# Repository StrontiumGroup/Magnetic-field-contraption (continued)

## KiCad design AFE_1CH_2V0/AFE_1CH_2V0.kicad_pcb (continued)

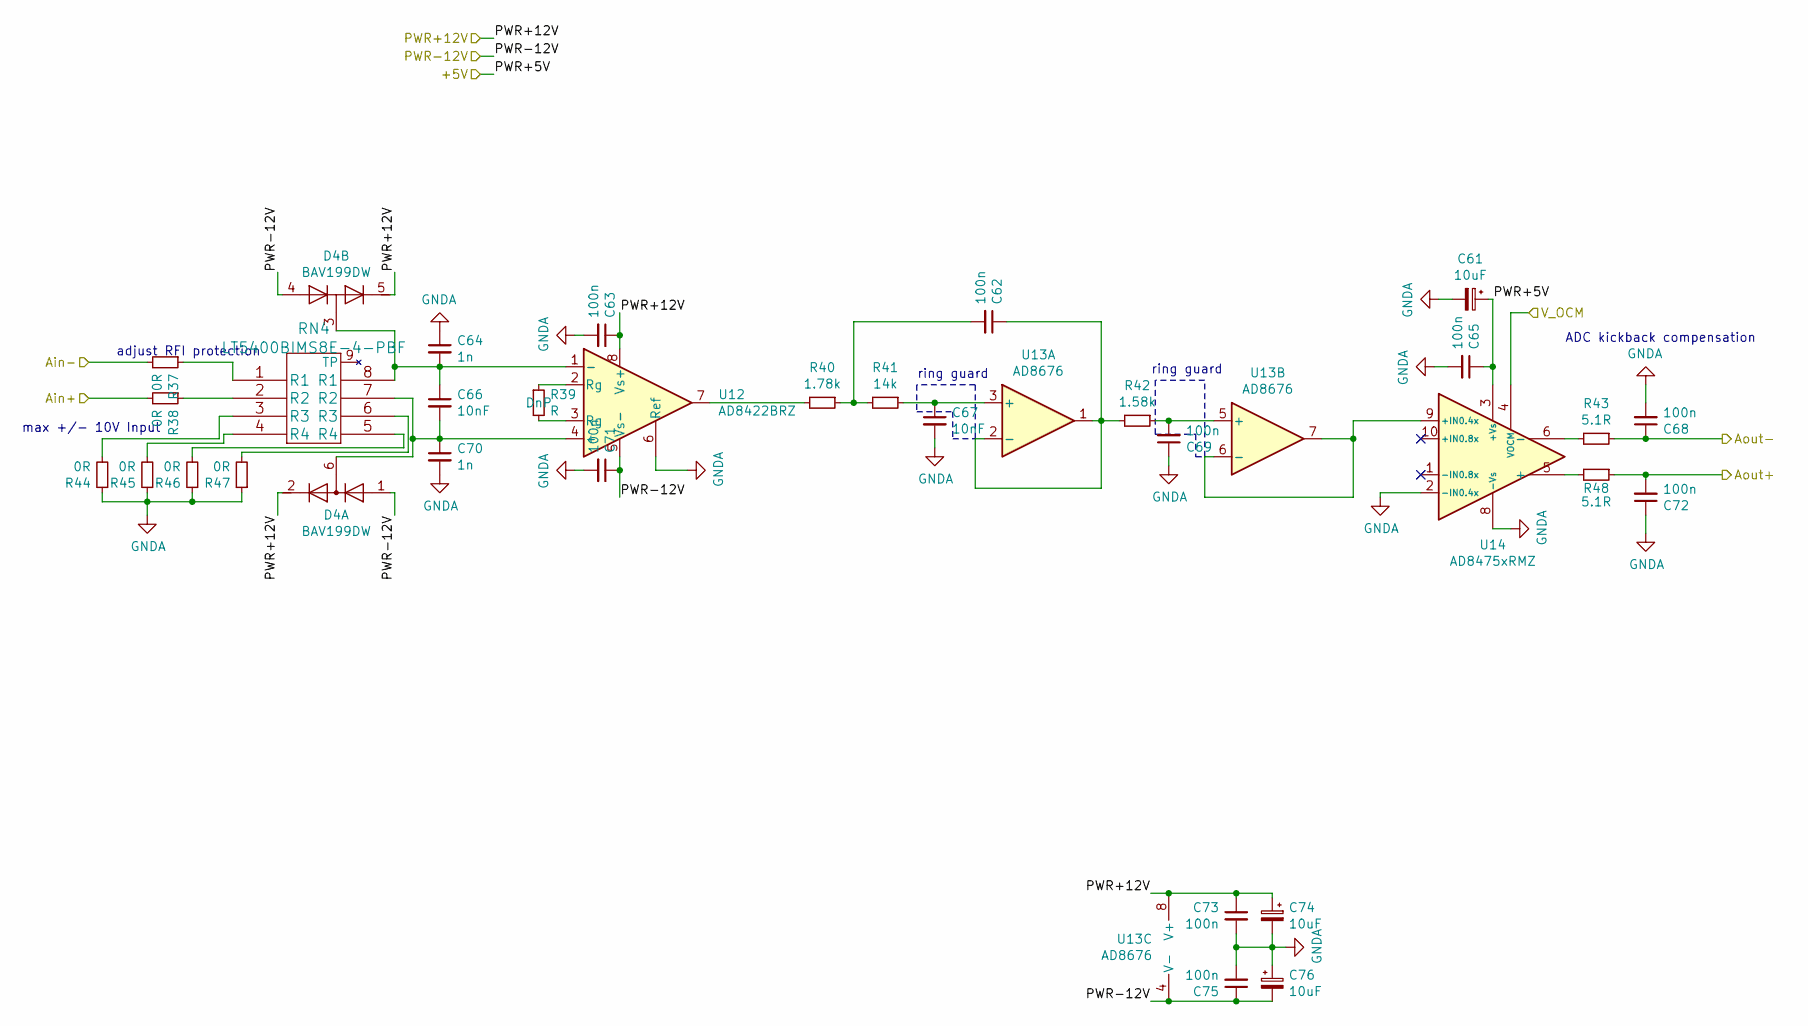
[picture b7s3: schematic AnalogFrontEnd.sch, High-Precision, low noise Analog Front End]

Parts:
C13, C26, C28: 10uF; CP_Elec_4x5.4; DigiKey 399-6695-1-ND
C14, C15, C20, C21, C23, C24: 100n; C_0805_2012Metric; DigiKey 399-1171-1-ND
C16, C22: 1n; C_0805_2012Metric; DigiKey 1276-1020-1-ND
C17, C25, C27: 100n; C_0805_2012Metric; DigiKey 399-1169-1-ND
C18, C19: 10nF; C_0805_2012Metric; DigiKey 1276-1245-1-ND
D1: BAV199DW; SOT-363_SC-70-6; DigiKey BAV199DW-FDITR-ND
R1, R2, R8, R9, R10, R11: 0R; R_0603_1608Metric; DigiKey 311-0.0GRCT-ND
R3: R; R_0805_2012Metric
R4: 1.78k; R_0805_2012Metric; DigiKey 541-1.78KCCT-ND
R5: 14k; R_0805_2012Metric; DigiKey 541-14.0KCCT-ND
R6: 1.58k; R_0805_2012Metric; DigiKey 541-1.58KCCT-ND
R7, R12: 5.1R; R_0805_2012Metric; DigiKey 541-5.10CCCT-ND
RN1: LT5400BIMS8E-4-PBF; MSOP-8-1EP_3x3mm_P0.65mm_EP1.68x1.88mm; DigiKey LT5400BIMS8E-4#PBF-ND
U3: AD8422BRZ; SOIC-8_3.9x4.9mm_P1.27mm; DigiKey AD8422ARZ-R7CT-ND
U4: AD8676; SOIC-8_3.9x4.9mm_P1.27mm
U5: AD8475xRMZ; MSOP-10_3x3mm_P0.5mm

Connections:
/AFE1/Ain+: R2.2; also elsewhere on the board
/AFE1/Ain-: R1.2; also elsewhere on the board
/AFE1/Aout+: C24.2, R12.1; also elsewhere on the board
/AFE1/Aout-: C20.1, R7.1; also elsewhere on the board
/PWR+5V: C13.1, C17.1, U5.3 (+Vs); also elsewhere on the board
/PWR+12V: C15.1, C25.1, C26.1, D1.2 (K2), D1.5 (K4), U3.8 (Vs+), U4.8 (V+); also elsewhere on the board
/PWR-12V: C23.1, C27.1, C28.2, D1.1 (A1), D1.4 (A3), U3.5 (Vs-), U4.4 (V-); also elsewhere on the board
/V_OCM: U5.4 (VOCM); also elsewhere on the board
GNDA: C13.2, C15.2, C16.1, C17.2, C19.2, C20.2, C21.1, C22.2, C23.2, C24.1, C25.2, C26.2, C27.2, C28.1, R8.1, R9.1, R10.1, R11.1, U3.6 (Ref), U5.2 (-IN0.4x), U5.8 (-Vs); also elsewhere on the board
unnamed: C14.1, R6.2, U4.1, U4.2 (-)
unnamed: C14.2, R4.1, R5.2
unnamed: C16.2, C18.1, D1.3 (K1A2), RN1.8 (R1), U3.1 (-)
unnamed: C18.2, C22.1, D1.6 (K3A4), RN1.7 (R2), U3.4 (+)
unnamed: C19.1, R5.1, U4.3 (+)
unnamed: C21.2, R6.1, U4.5 (+)
unnamed: R1.1, RN1.1 (R1)
unnamed: R2.1, RN1.2 (R2)
unnamed: R3.1, U3.2 (Rg)
unnamed: R3.2, U3.3 (Rg)
unnamed: R4.2, U3.7
unnamed: R7.2, U5.6 (-)
unnamed: R8.2, RN1.3 (R3)
unnamed: R9.2, RN1.4 (R4)
unnamed: R10.2, RN1.5 (R4)
unnamed: R11.2, RN1.6 (R3)
unnamed: R12.2, U5.5 (+)
unnamed: U4.6 (-), U4.7, U5.9 (+IN0.4x)

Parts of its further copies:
C29, C42, C44, C45, C58, C60, C61, C74, C76: 10uF; CP_Elec_4x5.4; DigiKey 399-6695-1-ND
C30, C31, C36, C37, C39, C40, C46, C47, C52, C53, C55, C56, C62, C63, C68, C69, C71, C72: 100n; C_0805_2012Metric; DigiKey 399-1171-1-ND
C32, C38, C48, C54, C64, C70: 1n; C_0805_2012Metric; DigiKey 1276-1020-1-ND
C33, C41, C43, C49, C57, C59, C65, C73, C75: 100n; C_0805_2012Metric; DigiKey 399-1169-1-ND
C34, C35, C50, C51, C66, C67: 10nF; C_0805_2012Metric; DigiKey 1276-1245-1-ND
D2, D3, D4: BAV199DW; SOT-363_SC-70-6; DigiKey BAV199DW-FDITR-ND
R13, R14, R20, R21, R22, R23, R25, R26, R32, R33, R34, R35, R37, R38, R44, R45, R46, R47: 0R; R_0603_1608Metric; DigiKey 311-0.0GRCT-ND
R15, R27, R39: R; R_0805_2012Metric
R16, R28, R40: 1.78k; R_0805_2012Metric; DigiKey 541-1.78KCCT-ND
R17, R29, R41: 14k; R_0805_2012Metric; DigiKey 541-14.0KCCT-ND
R18, R30, R42: 1.58k; R_0805_2012Metric; DigiKey 541-1.58KCCT-ND
R19, R24, R31, R36, R43, R48: 5.1R; R_0805_2012Metric; DigiKey 541-5.10CCCT-ND
RN2, RN3, RN4: LT5400BIMS8E-4-PBF; MSOP-8-1EP_3x3mm_P0.65mm_EP1.68x1.88mm; DigiKey LT5400BIMS8E-4#PBF-ND
U6, U9, U12: AD8422BRZ; SOIC-8_3.9x4.9mm_P1.27mm; DigiKey AD8422ARZ-R7CT-ND
U7, U10, U13: AD8676; SOIC-8_3.9x4.9mm_P1.27mm
U8, U11, U14: AD8475xRMZ; MSOP-10_3x3mm_P0.5mm

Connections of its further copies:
/AFE2/Ain+: R14.2; also elsewhere on the board
/AFE2/Ain-: R13.2; also elsewhere on the board
/AFE2/Aout+: C40.2, R24.1; also elsewhere on the board
/AFE2/Aout-: C36.1, R19.1; also elsewhere on the board
/AFE3/Ain+: R26.2; also elsewhere on the board
/AFE3/Ain-: R25.2; also elsewhere on the board
/AFE3/Aout+: C56.2, R36.1; also elsewhere on the board
/AFE3/Aout-: C52.1, R31.1; also elsewhere on the board
/AFE4/Ain+: R38.2; also elsewhere on the board
/AFE4/Ain-: R37.2; also elsewhere on the board
/AFE4/Aout+: C72.2, R48.1; also elsewhere on the board
/AFE4/Aout-: C68.1, R43.1; also elsewhere on the board
/PWR+5V: C29.1, C33.1, C45.1, C49.1, C61.1, C65.1, U8.3 (+Vs), U11.3 (+Vs), U14.3 (+Vs); also elsewhere on the board
/PWR+12V: C31.1, C41.1, C42.1, C47.1, C57.1, C58.1, C63.1, C73.1, C74.1, D2.2 (K2), D2.5 (K4), D3.2 (K2), D3.5 (K4), D4.2 (K2), D4.5 (K4), U6.8 (Vs+), U7.8 (V+), U9.8 (Vs+), U10.8 (V+), U12.8 (Vs+), U13.8 (V+); also elsewhere on the board
/PWR-12V: C39.1, C43.1, C44.2, C55.1, C59.1, C60.2, C71.1, C75.1, C76.2, D2.1 (A1), D2.4 (A3), D3.1 (A1), D3.4 (A3), D4.1 (A1), D4.4 (A3), U6.5 (Vs-), U7.4 (V-), U9.5 (Vs-), U10.4 (V-), U12.5 (Vs-), U13.4 (V-); also elsewhere on the board
/V_OCM: U8.4 (VOCM), U11.4 (VOCM), U14.4 (VOCM); also elsewhere on the board
GNDA: C29.2, C31.2, C32.1, C33.2, C35.2, C36.2, C37.1, C38.2, C39.2, C40.1, C41.2, C42.2, C43.2, C44.1, C45.2, C47.2, C48.1, C49.2, C51.2, C52.2, C53.1, C54.2, C55.2, C56.1, C57.2, C58.2, C59.2, C60.1, C61.2, C63.2, C64.1, C65.2, C67.2, C68.2, C69.1, C70.2, C71.2, C72.1, C73.2, C74.2, C75.2, C76.1, R20.1, R21.1, R22.1, R23.1, R32.1, R33.1, R34.1, R35.1, R44.1, R45.1, R46.1, R47.1, U6.6 (Ref), U8.2 (-IN0.4x), U8.8 (-Vs), U9.6 (Ref), U11.2 (-IN0.4x), U11.8 (-Vs), U12.6 (Ref), U14.2 (-IN0.4x), U14.8 (-Vs); also elsewhere on the board
unnamed: C30.1, R18.2, U7.1, U7.2 (-)
unnamed: C30.2, R16.1, R17.2
unnamed: C32.2, C34.1, D2.3 (K1A2), RN2.8 (R1), U6.1 (-)
unnamed: C34.2, C38.1, D2.6 (K3A4), RN2.7 (R2), U6.4 (+)
unnamed: C35.1, R17.1, U7.3 (+)
unnamed: C37.2, R18.1, U7.5 (+)
unnamed: C46.1, R30.2, U10.1, U10.2 (-)
unnamed: C46.2, R28.1, R29.2
unnamed: C48.2, C50.1, D3.3 (K1A2), RN3.8 (R1), U9.1 (-)
unnamed: C50.2, C54.1, D3.6 (K3A4), RN3.7 (R2), U9.4 (+)
unnamed: C51.1, R29.1, U10.3 (+)
unnamed: C53.2, R30.1, U10.5 (+)
unnamed: C62.1, R42.2, U13.1, U13.2 (-)
unnamed: C62.2, R40.1, R41.2
unnamed: C64.2, C66.1, D4.3 (K1A2), RN4.8 (R1), U12.1 (-)
unnamed: C66.2, C70.1, D4.6 (K3A4), RN4.7 (R2), U12.4 (+)
unnamed: C67.1, R41.1, U13.3 (+)
unnamed: C69.2, R42.1, U13.5 (+)
unnamed: R13.1, RN2.1 (R1)
unnamed: R14.1, RN2.2 (R2)
unnamed: R15.1, U6.2 (Rg)
unnamed: R15.2, U6.3 (Rg)
unnamed: R16.2, U6.7
unnamed: R19.2, U8.6 (-)
unnamed: R20.2, RN2.3 (R3)
unnamed: R21.2, RN2.4 (R4)
unnamed: R22.2, RN2.5 (R4)
unnamed: R23.2, RN2.6 (R3)
unnamed: R24.2, U8.5 (+)
unnamed: R25.1, RN3.1 (R1)
unnamed: R26.1, RN3.2 (R2)
unnamed: R27.1, U9.2 (Rg)
unnamed: R27.2, U9.3 (Rg)
unnamed: R28.2, U9.7
unnamed: R31.2, U11.6 (-)
unnamed: R32.2, RN3.3 (R3)
unnamed: R33.2, RN3.4 (R4)
unnamed: R34.2, RN3.5 (R4)
unnamed: R35.2, RN3.6 (R3)
unnamed: R36.2, U11.5 (+)
unnamed: R37.1, RN4.1 (R1)
unnamed: R38.1, RN4.2 (R2)
unnamed: R39.1, U12.2 (Rg)
unnamed: R39.2, U12.3 (Rg)
unnamed: R40.2, U12.7
unnamed: R43.2, U14.6 (-)
unnamed: R44.2, RN4.3 (R3)
unnamed: R45.2, RN4.4 (R4)
unnamed: R46.2, RN4.5 (R4)
unnamed: R47.2, RN4.6 (R3)
unnamed: R48.2, U14.5 (+)
unnamed: U7.6 (-), U7.7, U8.9 (+IN0.4x)
unnamed: U10.6 (-), U10.7, U11.9 (+IN0.4x)
unnamed: U13.6 (-), U13.7, U14.9 (+IN0.4x)

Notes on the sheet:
max +/- 10V Input
adjust RFI protection
ADC kickback compensation
ring guard

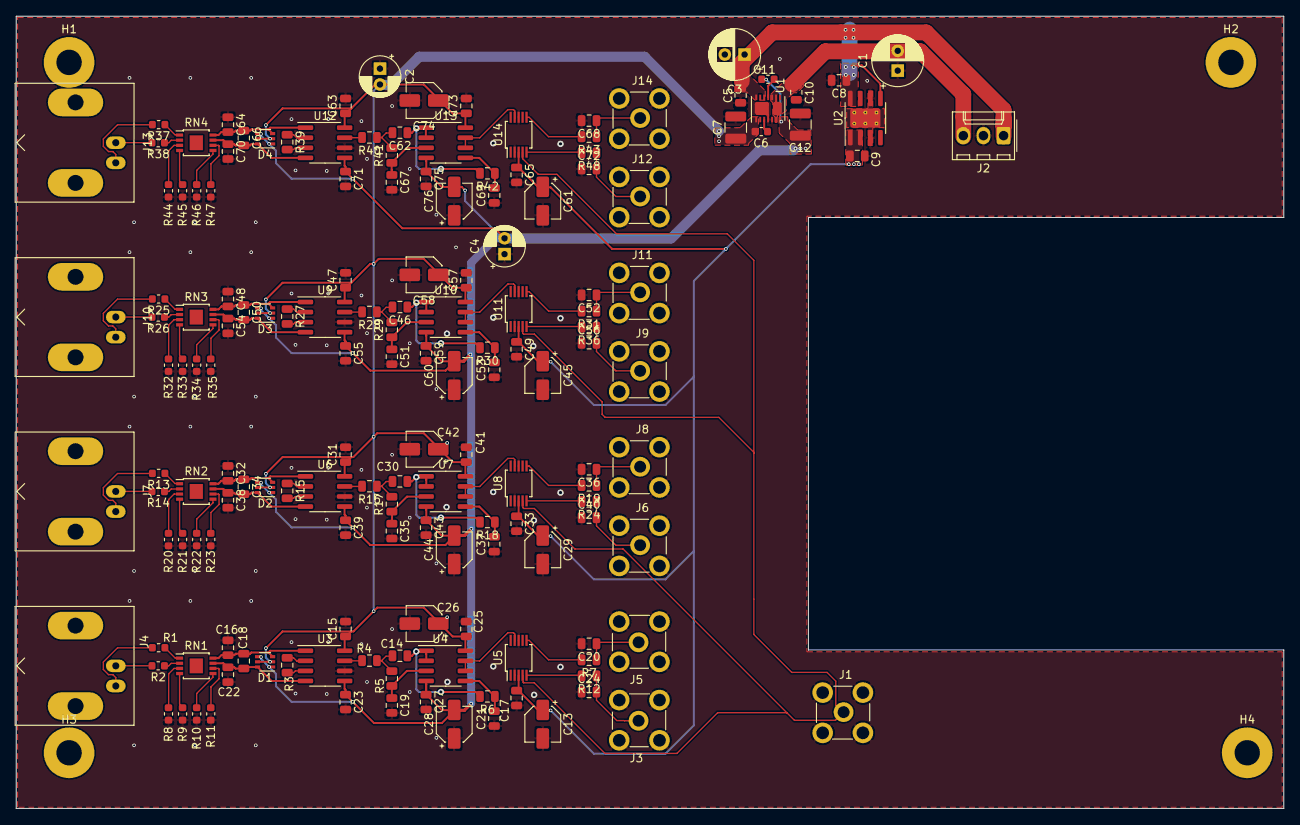
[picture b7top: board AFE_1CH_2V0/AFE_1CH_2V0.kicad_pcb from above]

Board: 4 copper layers, 160.0 x 100.0 mm, 164 parts (0 on the bottom side), 97 nets.
